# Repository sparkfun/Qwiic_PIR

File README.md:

SparkFun Qwiic PIR - 1&micro;A (EKMB1107112) & 170&micro;A (EKMC4607112K)
========================================

<table class="table table-hover table-striped table-bordered">
    <tr align="center">
      <td></td>
      <td></td>
    </tr>
    <tr align="center">
      <td><a href="https://www.sparkfun.com/products/17375">SparkFun Qwiic PIR - 1&micro;A (EKMB1107112)</a></td>
      <td><a href="https://www.sparkfun.com/products/17374">SparkFun Qwiic PIR - 170&micro;A (EKMC4607112K)</a></td>
    </tr>
</table>

The SparkFun Qwiic PIRs feature low-profile EKM-series PIR sensors from Panasonic for motion sensing projects using I<sup>2</sup>C. The two versions offer motion-sensing options for both battery powered (SparkFun Qwiic PIR - 1&micro;A (EKMB1107112)) and continuously powered (SparkFun Qwiic PIR - 170&micro;A (EKMC4607112K)) applications. The Qwiic PIR features an ATTiny84 to translate the PIR's digital output signal into I<sup>2</sup>C data so it can be integrated into an existing Qwiic or I<sup>2</sup>C bus.

Repository Contents
-------------------

* **/Documentation** - Data sheets, additional product information
* **/Firmware** - Qwiic PIR Firmware
* **/Hardware** - Eagle design files (.brd, .sch)
* **/Production** - Production panel files (.brd)

Documentation
--------------
* **[Qwiic PIR Arduino Library](https://github.com/sparkfun/SparkFun_Qwiic_PIR_Arduino_Library)** - Arduino library for the SparkFun Qwiic PIR.
* **[Qwiic PIR Python Library](https://github.com/sparkfun/Qwiic_PIR_Py)** - Python library for the SparkFun Qwiic PIR.
* **[Hookup Guide](https://learn.sparkfun.com/tutorials/qwiic-pir-hookup-guide)** - Basic hookup guide for the SparkFun Qwiic PIR.
* **[SparkFun Fritzing repo](https://github.com/sparkfun/Fritzing_Parts)** - Fritzing diagrams for SparkFun products.

Product Versions
----------------
* [SEN-17374](https://www.sparkfun.com/products/17374) - 170&micro;A version
* [SEN-17375](https://www.sparkfun.com/products/17375) - 1&micro;A version

Version History
---------------
* [v10](https://www.sparkfun.com/products/17374) - Initial release of SparkFun Qwiic PIR - 170&micro;A

License Information
-------------------

This product is _**open source**_! 

Please review the LICENSE.md file for license information. 

If you have any questions or concerns on licensing, please contact technical support on our [SparkFun forums](https://forum.sparkfun.com/viewforum.php?f=152).

Distributed as-is; no warranty is given.

- Your friends at SparkFun.

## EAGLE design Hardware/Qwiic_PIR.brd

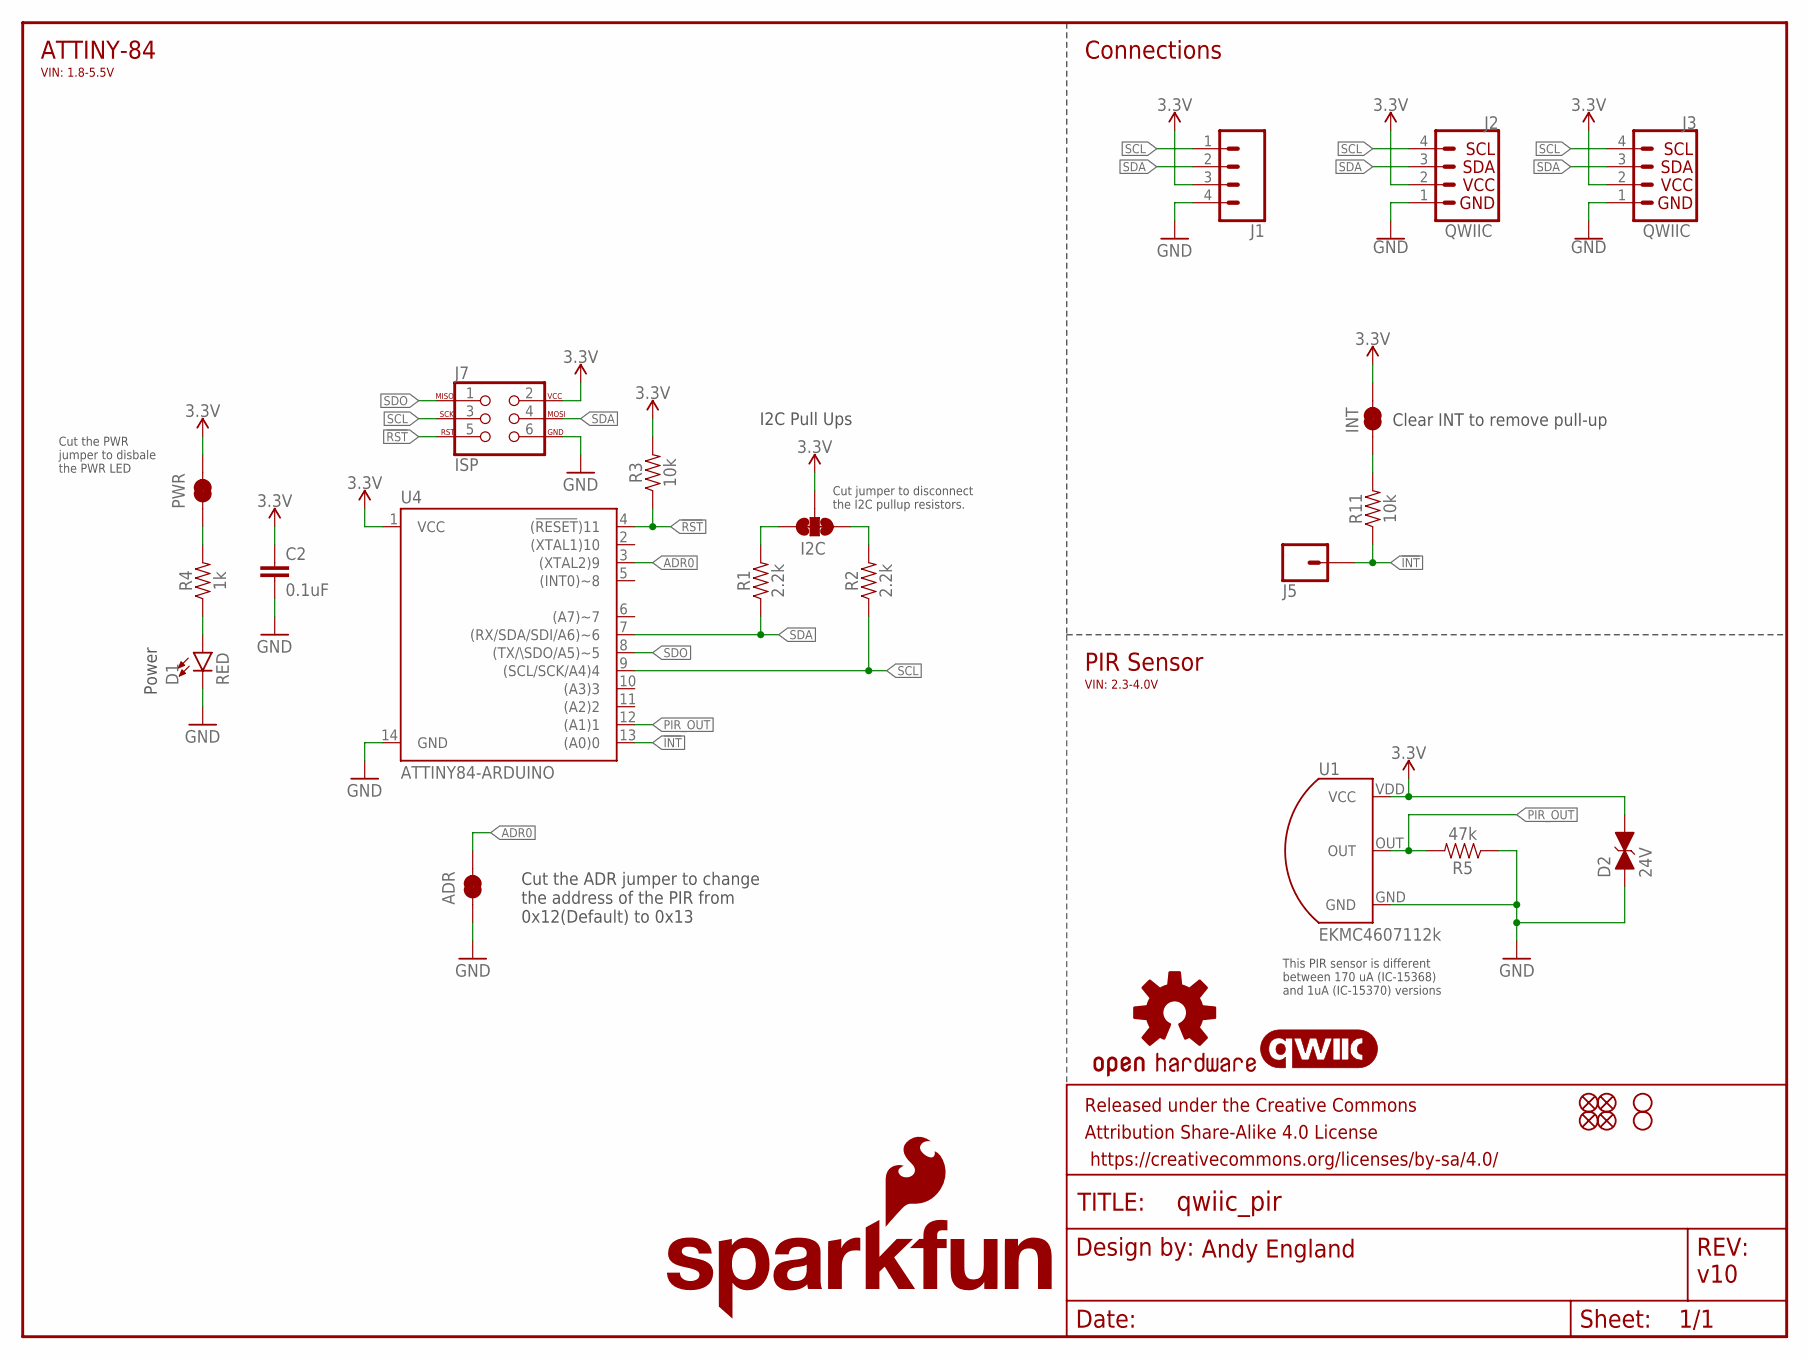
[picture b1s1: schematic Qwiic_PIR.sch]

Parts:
ADR: JUMPER-SMT_2_NC_TRACE_SILK; SMT-JUMPER_2_NC_TRACE_SILK
C2: 0.1uF; 0603
D1: RED; LED-0603
D2: 24V; 0603
FRAME1: FRAME-LETTER; CREATIVE_COMMONS
H1, H2: STAND-OFF
I2C: JUMPER-SMT_3_2-NC_TRACE_SILK; SMT-JUMPER_3_2-NC_TRACE_SILK
INT: JUMPER-SMT_2_NC_TRACE_SILK; SMT-JUMPER_2_NC_TRACE_SILK
J1: CONN_041X04_NO_SILK; 1X04_NO_SILK
J2, J3: QWIIC; JST04_1MM_RA
J5: CONN_01PTH_NO_SILK_YES_STOP; 1X01_NO_SILK
J7: ISP; 2X3_TEST_POINTS
JP2, JP6, JP8, JP9: FIDUCIALUFIDUCIAL; MICRO-FIDUCIAL
LOGO1: OSHW-LOGOMINI; OSHW-LOGO-MINI
LOGO2: QWIIC_LOGO_5MM; QWIIC_5MM
LOGO3: SFE_LOGO_NAME.1_INCH; SFE_LOGO_NAME_.1
LOGO4: SFE_LOGO_FLAME.1_INCH; SFE_LOGO_FLAME_.1
PWR: JUMPER-SMT_2_NC_TRACE_SILK; SMT-JUMPER_2_NC_TRACE_SILK
R1, R2: 2.2k; 0603
R3, R11: 10k; 0603
R4: 1k; 0603
R5: 47k; 0603
U1: EKMC4607112k; TO-3
U4: ATTINY84-ARDUINO; SO14

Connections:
3.3V: C2.1, D2.2 (C), I2C.2, INT.2, J1.3, J2.2, J3.2, J7.2, PWR.2, R3.2, U1.VDD (VCC), U4.1 (VCC)
!INT: J5.1, R11.1, U4.13 ((A0)0)
!RST: J7.5, R3.1, U4.4 ((!RESET!)11)
ADR0: ADR.2, U4.3 ((XTAL2)9)
GND: ADR.1, C2.2, D1.C, D2.1 (A), J1.4, J2.1, J3.1, J7.6, R5.1, U1.GND, U4.14 (GND)
INT_R: INT.1, R11.2
unnamed: D1.A, R4.1
PIR_OUT: R5.2, U1.OUT, U4.12 ((A1)1)
SCL: J1.1, J2.4, J3.4, J7.3, R2.1, U4.9 ((SCL/SCK/A4)4)
SCL_PU1: I2C.1, R2.2
SDA: J1.2, J2.3, J3.3, J7.4, R1.1, U4.7 ((RX/SDA/SDI/A6)~6)
SDA_PU1: I2C.3, R1.2
SDO: J7.1, U4.8 ((TX/\SDO/A5)~5)
STAT: PWR.1, R4.2

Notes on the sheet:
v10
Connections
Cut jumper to disconnect the I2C pullup resistors.
Cut the ADR jumper to change the address of the PIR from 0x12(Default) to 0x13
I2C Pull Ups
Power
Clear INT to remove pull-up
Andy England
ATTINY-84
PIR Sensor
VIN: 1.8-5.5V
Cut the PWR jumper to disbale the PWR LED
VIN: 2.3-4.0V
This PIR sensor is different between 170 uA (IC-15368) and 1uA (IC-15370) versions

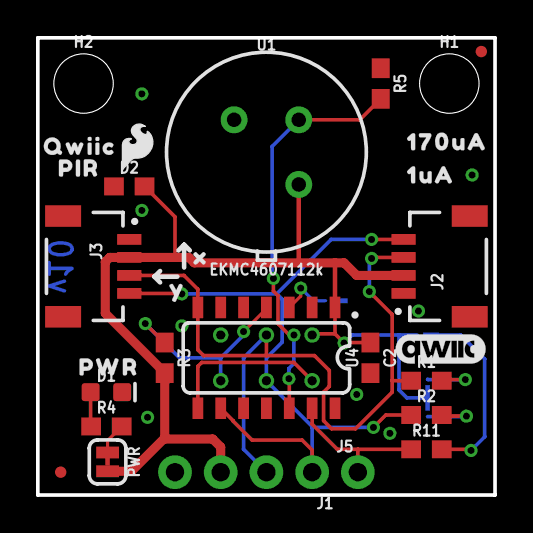
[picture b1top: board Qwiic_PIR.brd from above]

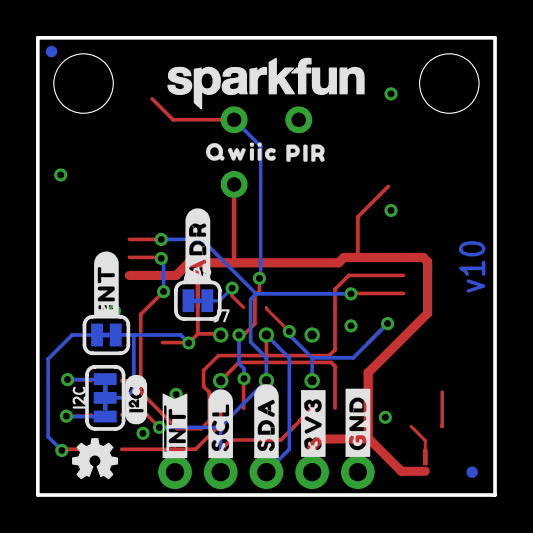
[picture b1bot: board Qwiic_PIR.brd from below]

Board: 2 copper layers, 25.4 x 25.4 mm, 48 parts (18 on the bottom side), 14 nets.

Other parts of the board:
U$1, U$13: PIR0
U$2: 170UA0
U$3: PWR0
U$4: #INT#0
U$5: #3V3#0
U$6: #SDA#0
U$7: #SCL#0
U$8: ##INT##0
U$9: 1UA0
U$10: I_SUPER2_C-()-03
U$11: #ADR#0
U$14: X0
U$16: Y0
U$17, U$18: QWIIC0
U$19: #GND#0

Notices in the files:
parts and their libraries:
SparkFun-Capacitors: Licensing: Creative Commons ShareAlike 4.0 International - https://creativecommons.org/licenses/by-sa/4.0
SparkFun-Aesthetics: Released under the Creative Commons Attribution Share-Alike 4.0 License
SparkFun-Aesthetics: https://creativecommons.org/licenses/by-sa/4.0
